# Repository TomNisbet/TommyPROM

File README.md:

# TommyPROM - An Arduino-based EEPROM programmer

This is a simple EEPROM programmer and reader that can be assembled using an Arduino and a
few additional parts.  The original code was specific to the 28C256 32Kx8 EEPROM, but it
has been extended to also support SST39SF040 Flash, many other EEPROMs and flash, and even
Intel 8755A EPROMS.

See the [documentation pages](https://tomnisbet.github.io/TommyPROM/) for the full
documentation with software, schematics, and troubleshooting tips.

Features include:
* Simple hardware design that can be assembled on a breadboard.
* ROM images transfers using XMODEM - no special host client needed.
* Support for fast block EEPROM writes - a 32K EEPROM will program in just a few seconds.
* Optimized code that supports the timing requirements needed to unlock the 28C series
[Software Protection Algorithm](https://tomnisbet.github.io/TommyPROM/docs/28C256-notes).
* Modular software design to easily support other EEPROM and EPROM families.

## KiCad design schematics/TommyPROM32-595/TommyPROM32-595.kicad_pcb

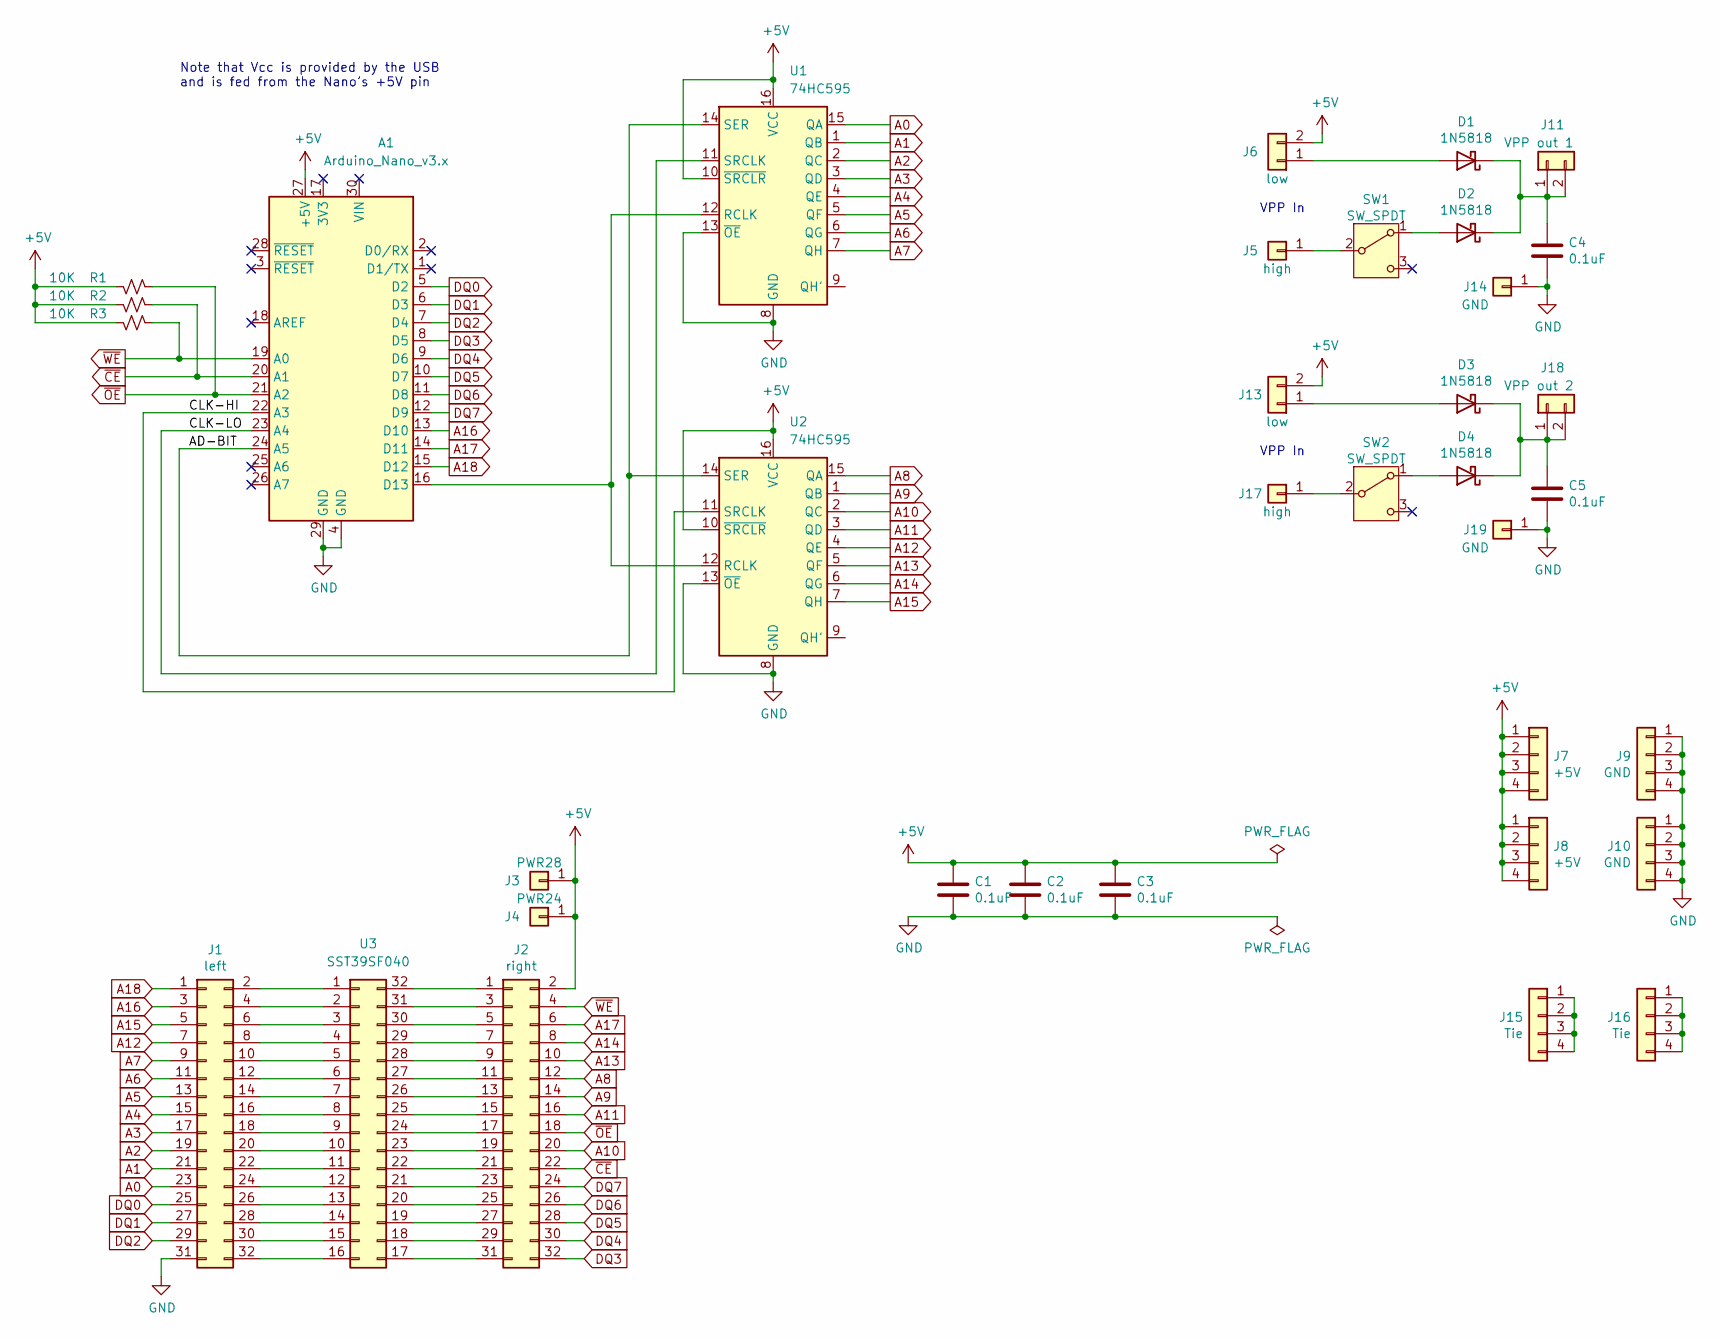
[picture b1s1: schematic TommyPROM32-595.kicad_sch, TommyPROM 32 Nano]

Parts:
A1: Arduino_Nano_v3.x; Arduino_Nano
C1, C2, C3, C4, C5: 0.1uF; C_Disc_D3.0mm_W1.6mm_P2.50mm
D1, D2, D3, D4: 1N5818; D_DO-41_SOD81_P10.16mm_Horizontal
J1: left; PinHeader_2x16_P2.54mm_Vertical
J2: right; PinHeader_2x16_P2.54mm_Vertical
J3: PWR28; PinHeader_1x01_P2.54mm_Vertical
J4: PWR24; PinHeader_1x01_P2.54mm_Vertical
J5, J17: high; PinHeader_1x01_P2.54mm_Vertical
J6, J13: low; PinHeader_1x02_P2.54mm_Vertical
J7, J8: +5V; PinHeader_1x04_P2.54mm_Vertical
J9, J10: GND; PinHeader_1x04_P2.54mm_Vertical
J11: VPP out 1; PinHeader_1x02_P2.54mm_Vertical
J14, J19: GND; PinHeader_1x01_P2.54mm_Vertical
J15, J16: Tie; PinHeader_1x04_P2.54mm_Vertical
J18: VPP out 2; PinHeader_1x02_P2.54mm_Vertical
R1, R2, R3: 10K; R_Axial_DIN0207_L6.3mm_D2.5mm_P10.16mm_Horizontal
SW1, SW2: SW_SPDT; Switch_Slide_11.6x4mm_EG1218
U1, U2: 74HC595; DIP-16_W7.62mm
U3: SST39SF040; DIP_Socket-32_W11.9_W12.7_W15.24_W17.78_W18.5_3M_232-1285-0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

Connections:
+5V: A1.27 (+5V), C1.1, C2.1, C3.1, J2.2, J3.1, J4.1, J6.2, J7.1, J7.2, J7.3, J7.4, J8.1, J8.2, J8.3, J8.4, J13.2, R1.1, R2.1, R3.1, U1.10 (~SRCLR), U1.16 (VCC), U2.10 (~SRCLR), U2.16 (VCC)
/AD-BIT: A1.24 (A5), U1.14 (SER), U2.14 (SER)
/CLK-HI: A1.22 (A3), U2.11 (SRCLK)
/CLK-LO: A1.23 (A4), U1.11 (SRCLK)
A0: J1.23, U1.15 (QA)
A1: J1.21, U1.1 (QB)
A2: J1.19, U1.2 (QC)
A3: J1.17, U1.3 (QD)
A4: J1.15, U1.4 (QE)
A5: J1.13, U1.5 (QF)
A6: J1.11, U1.6 (QG)
A7: J1.9, U1.7 (QH)
A8: J2.12, U2.15 (QA)
A9: J2.14, U2.1 (QB)
A10: J2.20, U2.2 (QC)
A11: J2.16, U2.3 (QD)
A12: J1.7, U2.4 (QE)
A13: J2.10, U2.5 (QF)
A14: J2.8, U2.6 (QG)
A15: J1.5, U2.7 (QH)
A16: A1.13 (D10), J1.3
A17: A1.14 (D11), J2.6
A18: A1.15 (D12), J1.1
DQ0: A1.5 (D2), J1.25
DQ1: A1.6 (D3), J1.27
DQ2: A1.7 (D4), J1.29
DQ3: A1.8 (D5), J2.32
DQ4: A1.9 (D6), J2.30
DQ5: A1.10 (D7), J2.28
DQ6: A1.11 (D8), J2.26
DQ7: A1.12 (D9), J2.24
GND: A1.4 (GND), A1.29 (GND), C1.2, C2.2, C3.2, C4.2, C5.2, J1.31, J9.1, J9.2, J9.3, J9.4, J10.1, J10.2, J10.3, J10.4, J14.1, J19.1, U1.8 (GND), U1.13 (~OE), U2.8 (GND), U2.13 (~OE)
unnamed: A1.16 (D13), U1.12 (RCLK), U2.12 (RCLK)
unnamed: D1.2 (A), J6.1
unnamed: C4.1, D1.1 (K), D2.1 (K), J11.1, J11.2
unnamed: D2.2 (A), SW1.1 (A)
unnamed: D3.2 (A), J13.1
unnamed: C5.1, D3.1 (K), D4.1 (K), J18.1, J18.2
unnamed: D4.2 (A), SW2.1 (A)
unnamed: J1.2, U3.1
unnamed: J1.4, U3.2
unnamed: J1.6, U3.3
unnamed: J1.8, U3.4
unnamed: J1.10, U3.5
unnamed: J1.12, U3.6
unnamed: J1.14, U3.7
unnamed: J1.16, U3.8
unnamed: J1.18, U3.9
unnamed: J1.20, U3.10
unnamed: J1.22, U3.11
unnamed: J1.24, U3.12
unnamed: J1.26, U3.13
unnamed: J1.28, U3.14
unnamed: J1.30, U3.15
unnamed: J1.32, U3.16
unnamed: J2.1, U3.32
unnamed: J2.3, U3.31
unnamed: J2.5, U3.30
unnamed: J2.7, U3.29
unnamed: J2.9, U3.28
unnamed: J2.11, U3.27
unnamed: J2.13, U3.26
unnamed: J2.15, U3.25
unnamed: J2.17, U3.24
unnamed: J2.19, U3.23
unnamed: J2.21, U3.22
unnamed: J2.23, U3.21
unnamed: J2.25, U3.20
unnamed: J2.27, U3.19
unnamed: J2.29, U3.18
unnamed: J2.31, U3.17
unnamed: J5.1, SW1.2 (B)
unnamed: J15.1, J15.2, J15.3, J15.4
unnamed: J16.1, J16.2, J16.3, J16.4
unnamed: J17.1, SW2.2 (B)
~CE: A1.20 (A1), J2.22, R2.2
~OE: A1.21 (A2), J2.18, R1.2
~WE: A1.19 (A0), J2.4, R3.2

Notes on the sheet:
Note that Vcc is provided by the USB and is fed from the Nano’s +5V pin
VPP In

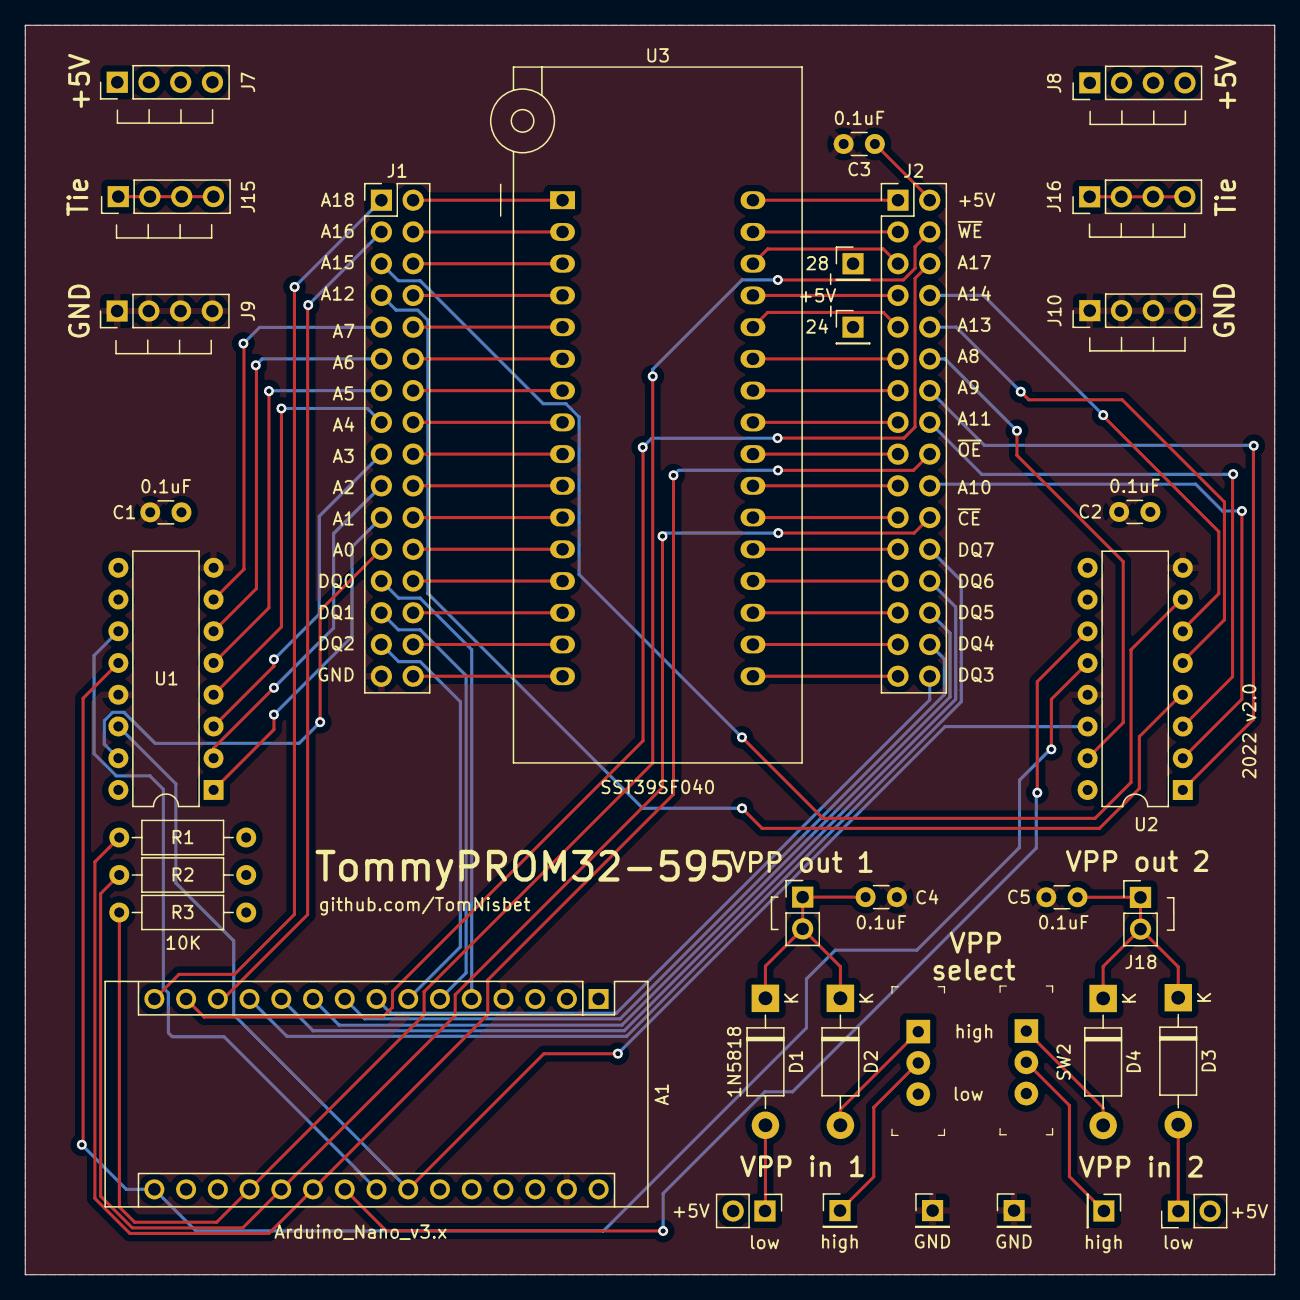
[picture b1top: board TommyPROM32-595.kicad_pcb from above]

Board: 2 copper layers, 100.0 x 100.0 mm, 36 parts (0 on the bottom side), 78 nets.

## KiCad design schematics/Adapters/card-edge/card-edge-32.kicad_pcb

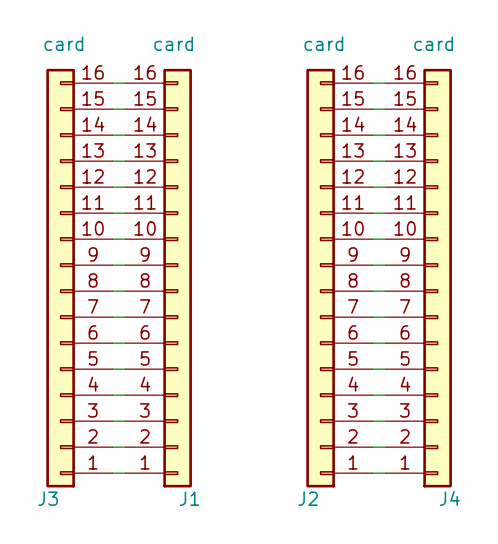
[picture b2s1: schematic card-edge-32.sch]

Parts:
J1, J2, J3, J4: card; PinHeader_1x16_P2.54mm_Vertical

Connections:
unnamed: J1.1, J3.1
unnamed: J1.2, J3.2
unnamed: J1.3, J3.3
unnamed: J1.4, J3.4
unnamed: J1.5, J3.5
unnamed: J1.6, J3.6
unnamed: J1.7, J3.7
unnamed: J1.8, J3.8
unnamed: J1.9, J3.9
unnamed: J1.10, J3.10
unnamed: J1.11, J3.11
unnamed: J1.12, J3.12
unnamed: J1.13, J3.13
unnamed: J1.14, J3.14
unnamed: J1.15, J3.15
unnamed: J1.16, J3.16
unnamed: J2.1, J4.1
unnamed: J2.2, J4.2
unnamed: J2.3, J4.3
unnamed: J2.4, J4.4
unnamed: J2.5, J4.5
unnamed: J2.6, J4.6
unnamed: J2.7, J4.7
unnamed: J2.8, J4.8
unnamed: J2.9, J4.9
unnamed: J2.10, J4.10
unnamed: J2.11, J4.11
unnamed: J2.12, J4.12
unnamed: J2.13, J4.13
unnamed: J2.14, J4.14
unnamed: J2.15, J4.15
unnamed: J2.16, J4.16

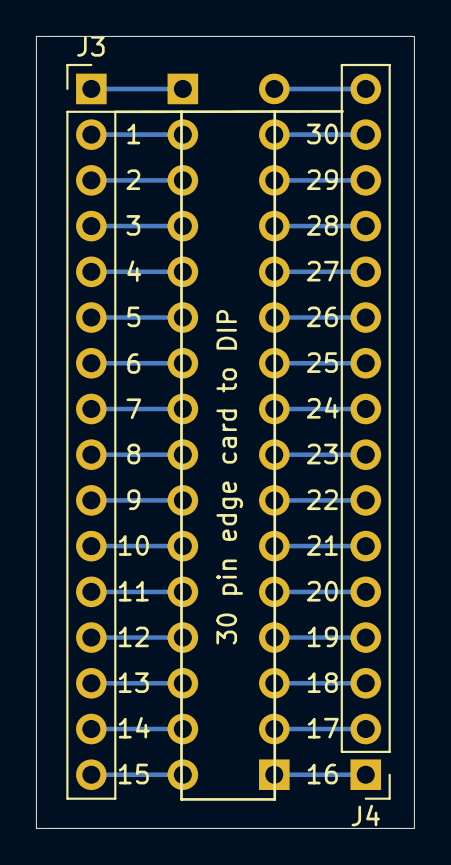
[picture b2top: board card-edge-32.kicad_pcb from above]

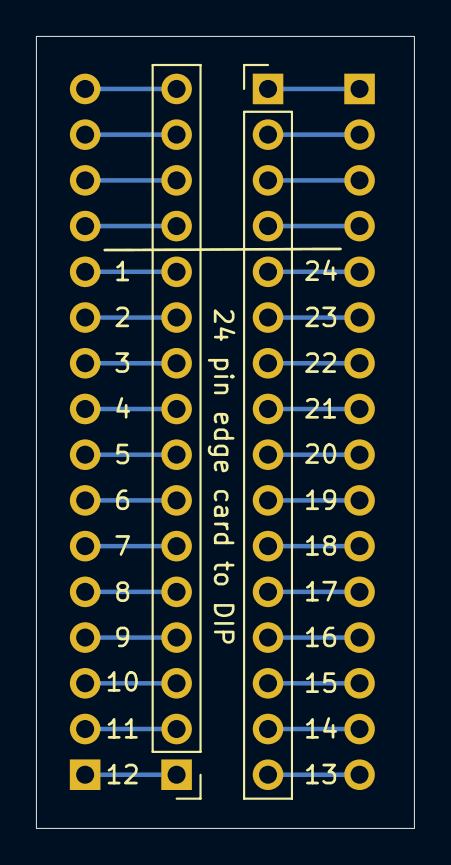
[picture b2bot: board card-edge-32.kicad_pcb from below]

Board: 2 copper layers, 21.0 x 44.0 mm, 4 parts (2 on the bottom side), 32 nets.

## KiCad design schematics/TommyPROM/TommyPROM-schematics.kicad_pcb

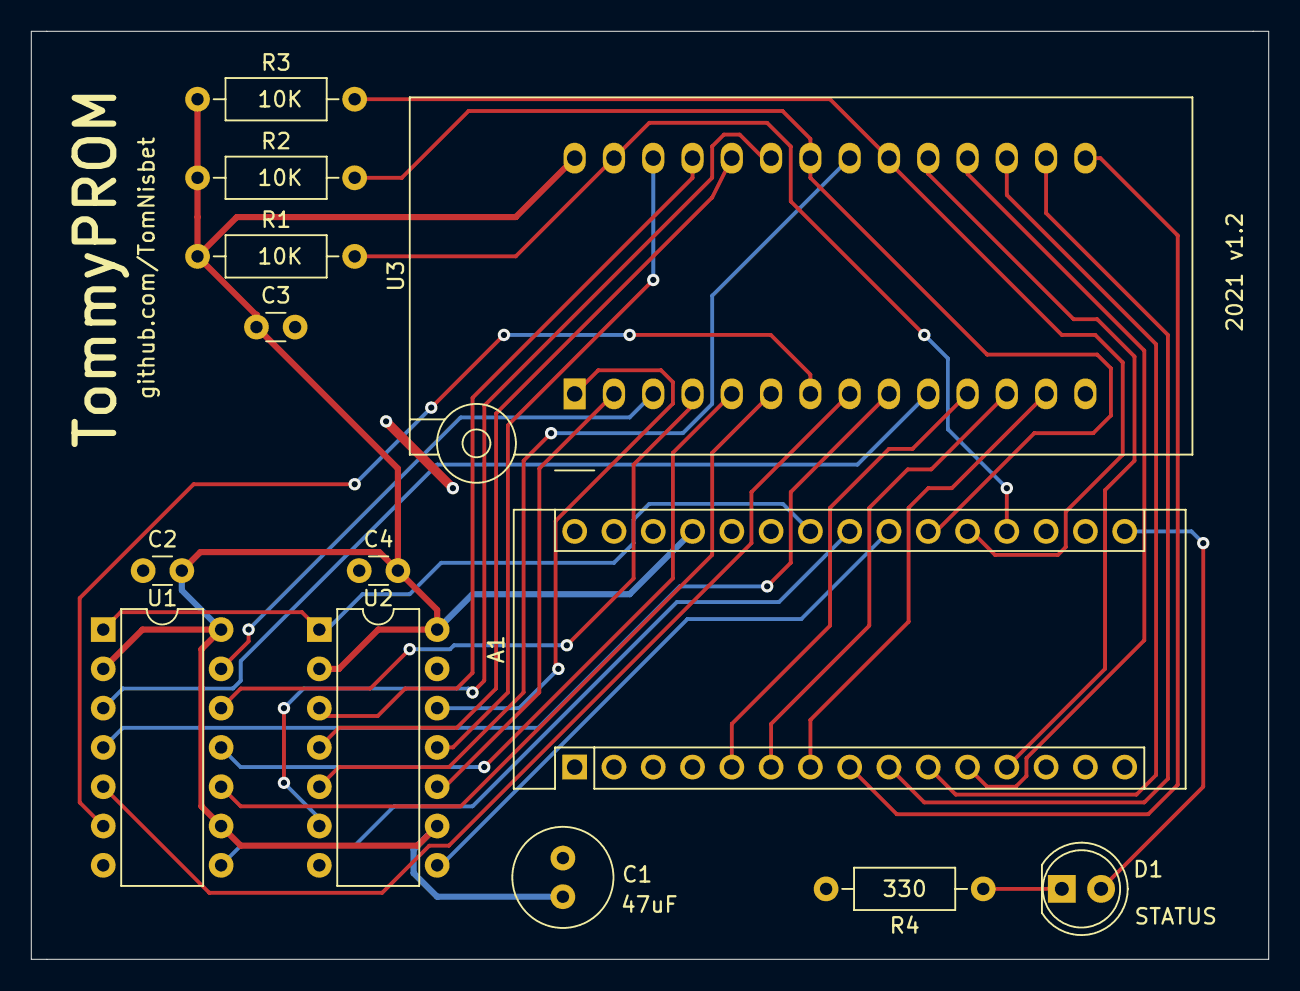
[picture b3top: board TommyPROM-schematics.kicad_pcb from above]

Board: 2 copper layers, 80.0 x 60.0 mm, 13 parts (0 on the bottom side), 33 nets.

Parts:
A1: Arduino_Nano_v3.x; Arduino_Nano
C1: 47uF; C_Radial_D6.3mm_H11.0mm_P2.50mm
C2, C3, C4: 0.1uF; C_Disc_D3.0mm_W1.6mm_P2.50mm
D1: STATUS; LED_D5.0mm
R1, R2, R3: 10K; R_Axial_DIN0207_L6.3mm_D2.5mm_P10.16mm_Horizontal
R4: 330; R_Axial_DIN0207_L6.3mm_D2.5mm_P10.16mm_Horizontal
U1, U2: 74HCT164; DIP-14_W7.62mm
U3: 28C256; DIP_Socket-28_W11.9_W12.7_W15.24_W17.78_W18.5_3M_228-1277-0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

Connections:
/A0: U1.3, U3.10
/A1: U1.4, U3.9
/A2: U1.5, U3.8
/A3: U1.6, U3.7
/A4: U1.10, U3.6
/A5: U1.11, U3.5
/A6: U1.12, U3.4
/A7: U1.13, U3.3
/A8: U2.3, U3.25
/A9: U2.4, U3.24
/A10: U2.5, U3.21
/A11: U2.6, U3.23
/A12: U2.10, U3.2
/A13: U2.11, U3.26
/A14: U2.12, U3.1
/AD-BIT: A1.24, U1.1, U2.1
/CE: A1.20, R3.2, U3.20
/CLK-HI: A1.22, U2.8
/CLK-LO: A1.23, U1.8
/D0: A1.5, U3.11
/D1: A1.6, U3.12
/D2: A1.7, U3.13
/D3: A1.8, U3.15
/D4: A1.9, U3.16
/D5: A1.10, U3.17
/D6: A1.11, U3.18
/D7: A1.12, U3.19
/OE: A1.21, R2.2, U3.22
/WE: A1.19, R1.2, U3.27
GND: A1.4, A1.29, C1.2, C2.2, C3.2, C4.2, R4.2, U1.7, U2.7, U3.14
unnamed: A1.16, D1.2
unnamed: D1.1, R4.1
VCC: A1.27, C1.1, C2.1, C3.1, C4.1, R1.1, R2.1, R3.1, U1.2, U1.9, U1.14, U2.2, U2.9, U2.14, U3.28

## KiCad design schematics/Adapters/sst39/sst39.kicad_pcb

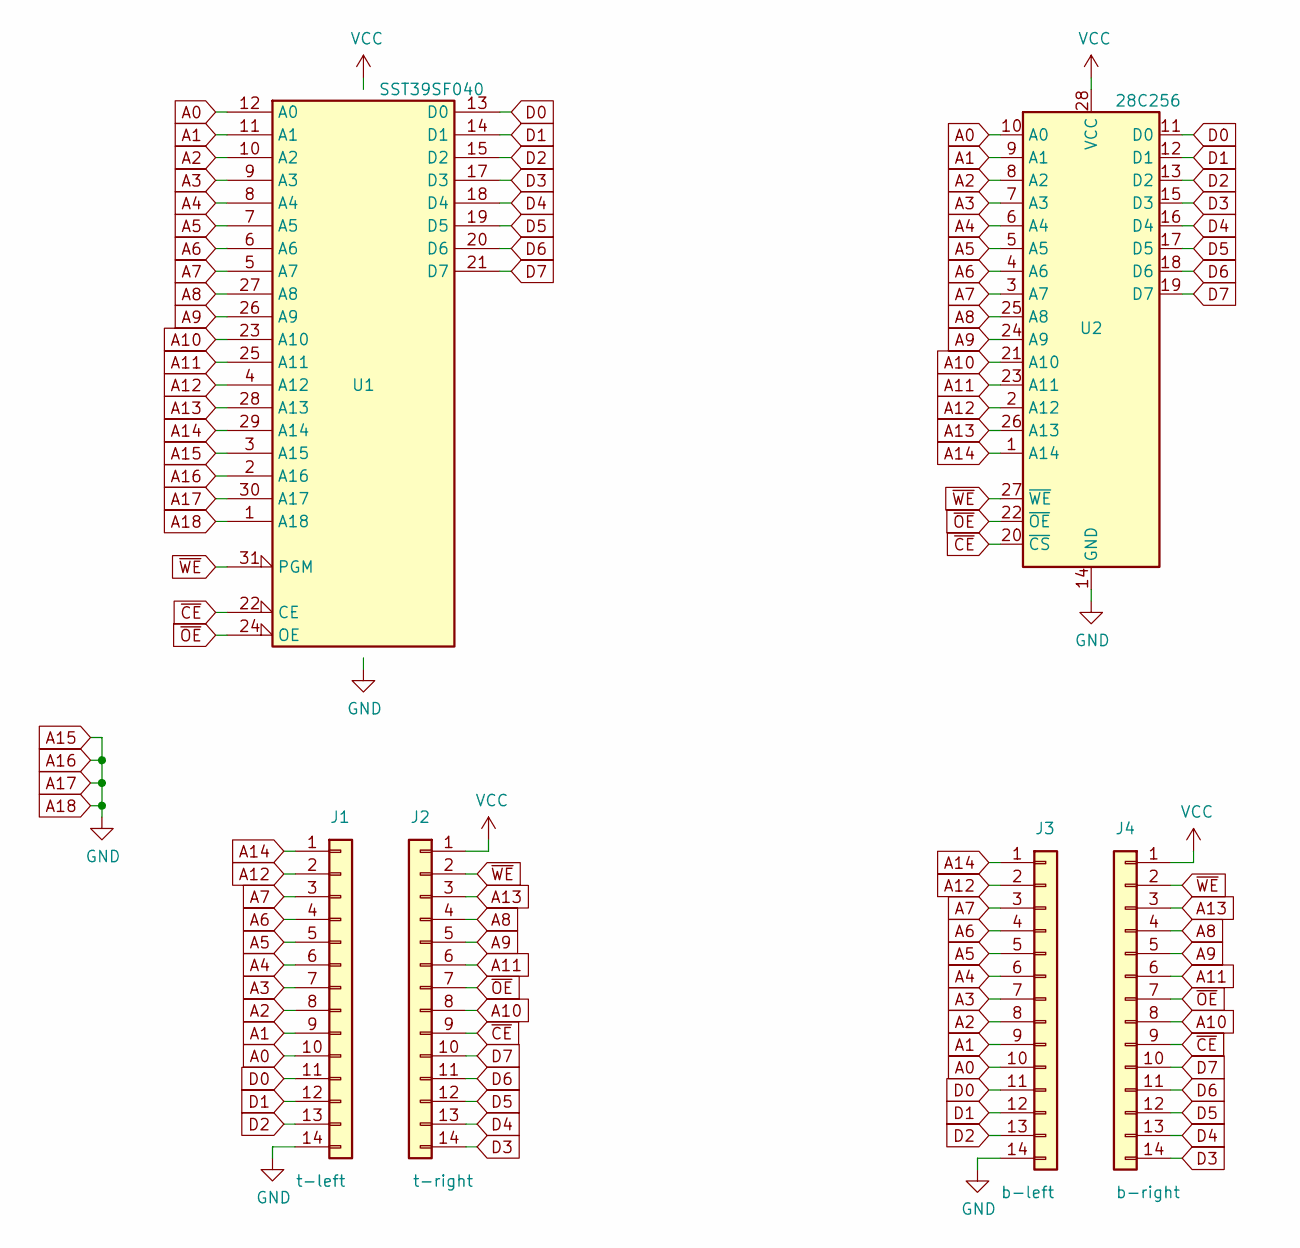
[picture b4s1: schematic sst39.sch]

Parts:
J1: t-left; PinHeader_1x14_P2.54mm_Vertical
J2: t-right; PinHeader_1x14_P2.54mm_Vertical
J3: b-left; PinSocket_1x14_P2.54mm_Vertical
J4: b-right; PinSocket_1x14_P2.54mm_Vertical
U1: SST39SF040; DIP-32_W15.24mm_Socket
U2: 28C256; DIP-28_W15.24mm

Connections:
A0: J1.10, J3.10, U1.12 (A0), U2.10 (A0)
A1: J1.9, J3.9, U1.11 (A1), U2.9 (A1)
A2: J1.8, J3.8, U1.10 (A2), U2.8 (A2)
A3: J1.7, J3.7, U1.9 (A3), U2.7 (A3)
A4: J1.6, J3.6, U1.8 (A4), U2.6 (A4)
A5: J1.5, J3.5, U1.7 (A5), U2.5 (A5)
A6: J1.4, J3.4, U1.6 (A6), U2.4 (A6)
A7: J1.3, J3.3, U1.5 (A7), U2.3 (A7)
A8: J2.4, J4.4, U1.27 (A8), U2.25 (A8)
A9: J2.5, J4.5, U1.26 (A9), U2.24 (A9)
A10: J2.8, J4.8, U1.23 (A10), U2.21 (A10)
A11: J2.6, J4.6, U1.25 (A11), U2.23 (A11)
A12: J1.2, J3.2, U1.4 (A12), U2.2 (A12)
A13: J2.3, J4.3, U1.28 (A13), U2.26 (A13)
A14: J1.1, J3.1, U1.29 (A14), U2.1 (A14)
A15: J1.14, J3.14, U1.1 (A18), U1.2 (A16), U1.3 (A15), U1.16 (GND), U1.30 (A17), U2.14 (GND)
D0: J1.11, J3.11, U1.13 (D0), U2.11 (D0)
D1: J1.12, J3.12, U1.14 (D1), U2.12 (D1)
D2: J1.13, J3.13, U1.15 (D2), U2.13 (D2)
D3: J2.14, J4.14, U1.17 (D3), U2.15 (D3)
D4: J2.13, J4.13, U1.18 (D4), U2.16 (D4)
D5: J2.12, J4.12, U1.19 (D5), U2.17 (D5)
D6: J2.11, J4.11, U1.20 (D6), U2.18 (D6)
D7: J2.10, J4.10, U1.21 (D7), U2.19 (D7)
VCC: J2.1, J4.1, U1.32 (VCC), U2.28 (VCC)
~CE: J2.9, J4.9, U1.22 (CE), U2.20 (~CS)
~OE: J2.7, J4.7, U1.24 (OE), U2.22 (~OE)
~WE: J2.2, J4.2, U1.31 (PGM), U2.27 (~WE)

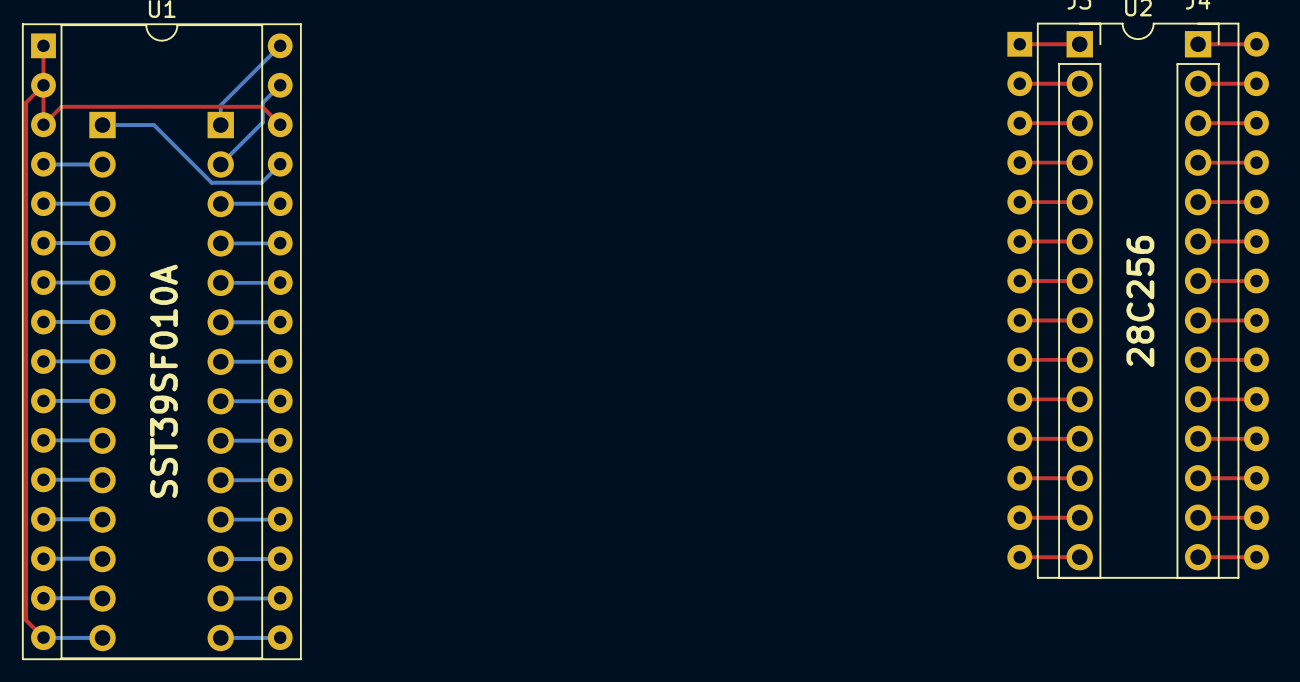
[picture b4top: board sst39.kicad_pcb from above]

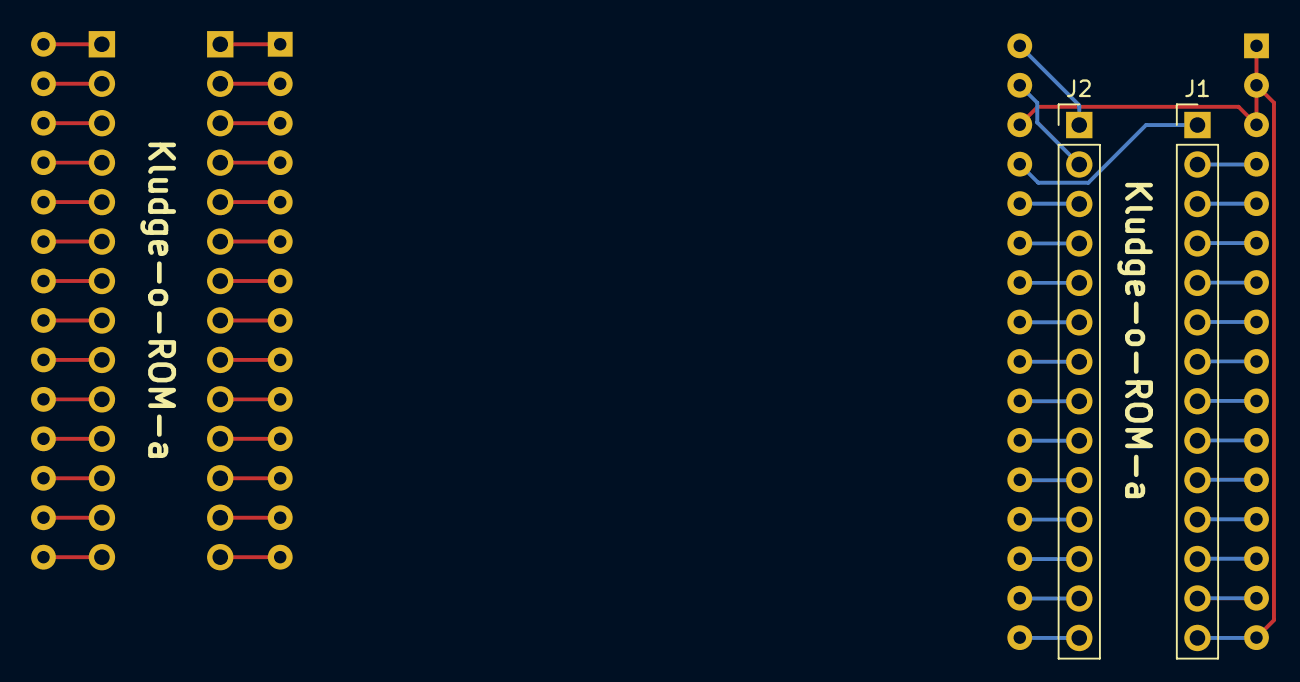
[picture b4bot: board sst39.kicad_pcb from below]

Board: 2 copper layers, 6 parts (2 on the bottom side), 28 nets.

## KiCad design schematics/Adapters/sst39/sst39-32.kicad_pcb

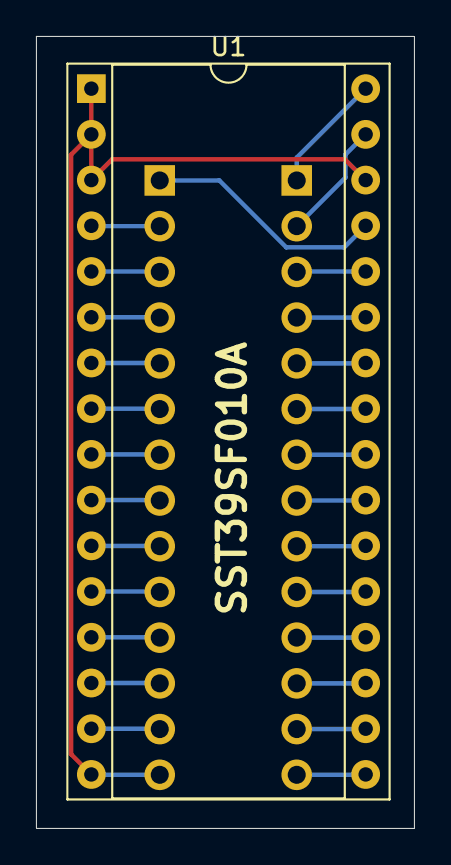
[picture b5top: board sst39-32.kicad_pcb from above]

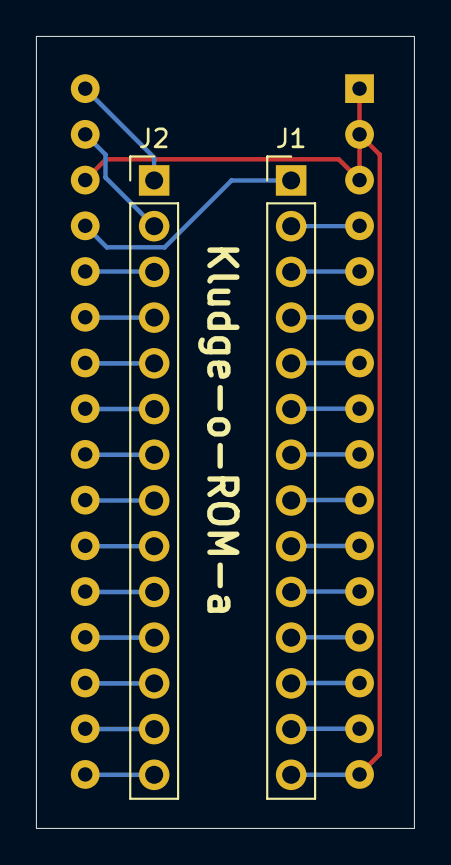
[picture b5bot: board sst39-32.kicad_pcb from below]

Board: 2 copper layers, 21.0 x 44.0 mm, 3 parts (2 on the bottom side), 28 nets.

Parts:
J1: t-left; PinHeader_1x14_P2.54mm_Vertical
J2: t-right; PinHeader_1x14_P2.54mm_Vertical
U1: SST39SF040; DIP-32_W15.24mm_Socket

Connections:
A0: J1.10, U1.12
A1: J1.9, U1.11
A2: J1.8, U1.10
A3: J1.7, U1.9
A4: J1.6, U1.8
A5: J1.5, U1.7
A6: J1.4, U1.6
A7: J1.3, U1.5
A8: J2.4, U1.27
A9: J2.5, U1.26
A10: J2.8, U1.23
A11: J2.6, U1.25
A12: J1.2, U1.4
A13: J2.3, U1.28
A14: J1.1, U1.29
A15: J1.14, U1.1, U1.2, U1.3, U1.16, U1.30
D0: J1.11, U1.13
D1: J1.12, U1.14
D2: J1.13, U1.15
D3: J2.14, U1.17
D4: J2.13, U1.18
D5: J2.12, U1.19
D6: J2.11, U1.20
D7: J2.10, U1.21
VCC: J2.1, U1.32
~CE: J2.9, U1.22
~OE: J2.7, U1.24
~WE: J2.2, U1.31

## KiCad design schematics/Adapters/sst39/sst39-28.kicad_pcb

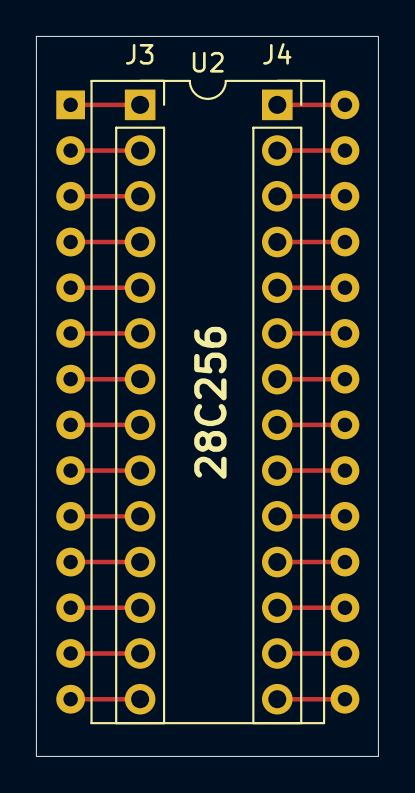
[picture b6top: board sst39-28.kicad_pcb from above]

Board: 2 copper layers, 19.0 x 40.0 mm, 3 parts (0 on the bottom side), 28 nets.

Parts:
J3: b-left; PinSocket_1x14_P2.54mm_Vertical
J4: b-right; PinSocket_1x14_P2.54mm_Vertical
U2: 28C256; DIP-28_W15.24mm

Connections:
A0: J3.10, U2.10
A1: J3.9, U2.9
A2: J3.8, U2.8
A3: J3.7, U2.7
A4: J3.6, U2.6
A5: J3.5, U2.5
A6: J3.4, U2.4
A7: J3.3, U2.3
A8: J4.4, U2.25
A9: J4.5, U2.24
A10: J4.8, U2.21
A11: J4.6, U2.23
A12: J3.2, U2.2
A13: J4.3, U2.26
A14: J3.1, U2.1
A15: J3.14, U2.14
D0: J3.11, U2.11
D1: J3.12, U2.12
D2: J3.13, U2.13
D3: J4.14, U2.15
D4: J4.13, U2.16
D5: J4.12, U2.17
D6: J4.11, U2.18
D7: J4.10, U2.19
VCC: J4.1, U2.28
~CE: J4.9, U2.20
~OE: J4.7, U2.22
~WE: J4.2, U2.27

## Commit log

2017-02-28 more README details
2018-05-11 Split code and add 8755 support
    Classes now in separate files
    PromDevice classes used to allow for a choice of hardware support
    ErasedCheck command
    Support for Intel 8755 EPROM
2018-05-11 Move sketch to appropriately named subfolder
    The Arduino IDE requires that a sketch be located in a folder of the same name. Although the name of the repository does match the sketch name, when GitHub's popular Clone or download > Download ZIP 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
    When opening a file that does not meet this sketch/folder name matching requirement the Arduino IDE presents a dialog:
    The file "TommyPROM.ino" needs to be inside a sketch folder named "TommyPROM".
    Create this folder, move the file, and continue?
    After clicking "OK" the Arduino IDE currently moves only the file
2018-05-17 Update power switching on 8755A schematic and add missing Eagle file
2018-05-18 Update documentation for new modular code and 8755A support
2018-05-18 fix readme file name
2018-05-18 Formatting issues in extension.md
2018-05-18 Add links to the other READMEs to the top-level file
2018-12-20 Fix typo to define UNO platform
2018-12-20 Fix pin assignments on 8755A device to match the schematic
2018-12-20 Fix schematic label errors and pin assignments on 8755A device to match the schematic
2018-12-22 Fix address error with 8755A burning
2019-05-16 Update hardware readme with shift register info
2019-06-03 Fix broken link to extenstions README
2019-06-03 Minor grammar fixes
2019-06-09 Add lock command for 28C devices
2019-06-09 Add Hardware Verify sketch
2019-06-09 Print elapsed time for unlock in hardware verifier
2019-06-10 Speed up setAddr code to meet SDP timing restrictions
2019-06-10 Update HW verifier readme
2019-06-16 Optimize Address Register code for 28C timing requirements
    Also remove slower generic Arduino code so that the project is now tied
    to specific Arduino versions.
    Add readme for 28C chips.
2019-06-20 Add devices to 28C readme
2019-06-24 List devices in 28C readme
2019-07-20 Extend addressing to 19 bits for larger chips like the 29C040
2020-01-30 Fixed not compiling when using 27xx profile
    I'm not sure if this is the correct fix but without this one line the code wouldn't compile and it would say that "data" wasn't declared.
2020-05-22 Fixes #8 - allow CR or LF as the terminal EOL character
2020-06-28 Set theme jekyll-theme-minimal
2020-06-28 github pages config
2020-06-28 Initial documentation pages
2020-06-29 Move readmes to the github pages
2020-06-29 Fix broken documentation links
2020-06-29 broken links and footer
2020-06-29 yaml config error
2020-06-29 broken links
2020-06-29 fixes #11 - ASCII dump missing character
2020-06-29 Add page descriptions to front matter
2020-07-17 Add detailed troubleshooting commands
2020-08-09 Utility sketch to disable SDP on Ben Eater hardware
2020-08-10 Update Unlock Ben Eater Hardware notes
2020-08-10 Update Unlock Ben Eater hardware readme
2020-08-10 Update 28C256 docs
2020-08-10 Update gitignore for Mac
2020-08-14 optimize Ben Eater unlock setAddress timing
2020-08-15 Fix #12 - add aemiller51's Poke command
2020-08-24 Add support for 74LS595 shift registers
2020-08-24 Issue #13 - fix HWverify CLI parsing and update documentation.
2020-08-24 Issue #14 - consume the ACK to the xmodem EOT when sending files.
2020-08-26 Fix #15 - typo in high address register pin definition.
2020-10-07 Add debug for XModem transfer failure
2020-10-11 Fix #17 - pulse both CE and OE during the write verify cycle.
2020-10-12 Add 74LS595 code to the HardwareVerify sketch
2020-10-12 Add some high-level commands to HardwareVerify sketch
2020-10-12 Fix #18 - addressing bug with 74LS595 shift registers
2020-10-14 Fix #19 - XModem changed from 16-bit CRC to 8-bit checksum
2020-11-11 File transfer default back to XModem-CRC for #20
2020-11-14 Issue #20 - TeraTerm XModem file transfers with W command.
2020-11-14 Note the connection of the 74LS595 G/OE pin
2020-11-27 Update hardware docs for issue #21
2020-11-27 commas matter
2021-04-30 redraw schematic in Kicad
2021-04-30 remove comment about missing connections
2021-04-30 make schematic image a link
2021-04-30 broken link
2021-05-05 pcb for review
2021-05-05 update pcb images
2021-05-05 v1.1 pcb images for review
2021-05-06 swap LED direction
2021-05-25 Add KiCad files
2021-05-27 add photo of the prototype 74LS595 build
2022-08-07 Update README.md
    add link to 28C256 notes
2022-08-13 Add preliminary support for SST39SF flash
2022-08-15 Updated documentation for 3.0
2022-08-15 fix image link
2022-08-15 re-order docs nav menu
2022-08-18 add PCB to documentation
2022-08-18 image link
2022-08-18 fix file name
2022-08-18 link typo
2022-08-18 add linkable images to docs
2022-08-18 new photo of PCB version
2022-11-25 Remove unused methods; update PCB photo
2022-11-25 Add PCB page to prep for new board
2022-11-25 broken link in docs
2022-11-25 doc updates for PCB
2022-12-03 schematics for TommyPROM32 and adapters
2022-12-07 doc links
2022-12-10 device support for 27E257/27C257
2022-12-12 expand chips tested list in docs
2022-12-12 TommyPROM32 PCB docs
2022-12-13 broken doc image links
2022-12-13 Add support for SST28SF SuperFlash
2022-12-14 Add support for SST27C0x0 flash chips
2022-12-22 Add W27C512
2023-01-20 gitignore updates
2023-01-20 V2.0 of the TommyPROM32 board
2023-07-15 update PgmType for 27C040 EPROM
    The (AMD/Atmel) 27C040 EPROM doesn't have a dedicated Write Enable (WE),
    instead sharing the same pin for CE# and PGM#. This updates the PromDevice27
    line for this device to use the E27C_PGM_CE PgmType.
    This configuration has been successfully used to read, program and verify an
    AM27C040 device. A +12.75V voltage was applied to Vpp during the duration of
    device programming.
2023-09-17 port docs to minumal-mistakes Jekyll theme
2023-09-17 add getting-started doc page
2023-09-17 broken image link
2023-09-18 Split Intel 8755 documentation out
2023-09-18 add prom-specific doc page
2023-09-18 more PROM details in docs
2023-09-18 Update prom-specific documentation
2023-09-18 Add chip manufacturer table to docs
2023-09-18 update manufacturers
2023-09-18 add TommyPROM32 schematic image
2023-09-19 update chip driver docs
2023-09-19 chip-specific docs
2023-09-20 add support for M27C256
2023-10-09 Update README.md to fix image links
2024-03-09 Fix broken link
2024-04-07 add 23xx support
2024-04-09 Automatic detection of 2316 chip selects
2024-04-10 more nuanced default command args
2024-04-10 cleanups
2024-04-10 fix gotchas with unspecified start
2024-04-10 fix from pr comment
2024-04-11 docs for PromDevice23 2316 ROMS
2024-04-12 only Dump command remembers where to pick up again
2024-04-12 rename next -> dump_next
2024-04-12 update 2316 page
2024-04-13 Add dedicated 2316 page and TommyPROM32 page
2024-04-13 inevitable broken doc links
2024-04-14 TommyPROM32 doc updates
2024-04-22 remove debug commands by default
2024-05-03 card edge connector schematic
2024-05-04 update 27_CE algorithm for overwrite pulses
2024-05-04 add M27256 to docs
2024-05-05 add to chips list in docs
2024-05-11 update device list
2024-05-17 split PromDevice docs to separate pages
2024-06-09 TommyPROM32 pcb/sch adapted for use with 74xx595 registers
2024-06-20 Fix ERC errors due to missing no connect flags
2024-09-16 Update design-350-tommyprom32-pcb.md
    Typo in M27C256 description
2025-04-13 broken link to new SDP page
